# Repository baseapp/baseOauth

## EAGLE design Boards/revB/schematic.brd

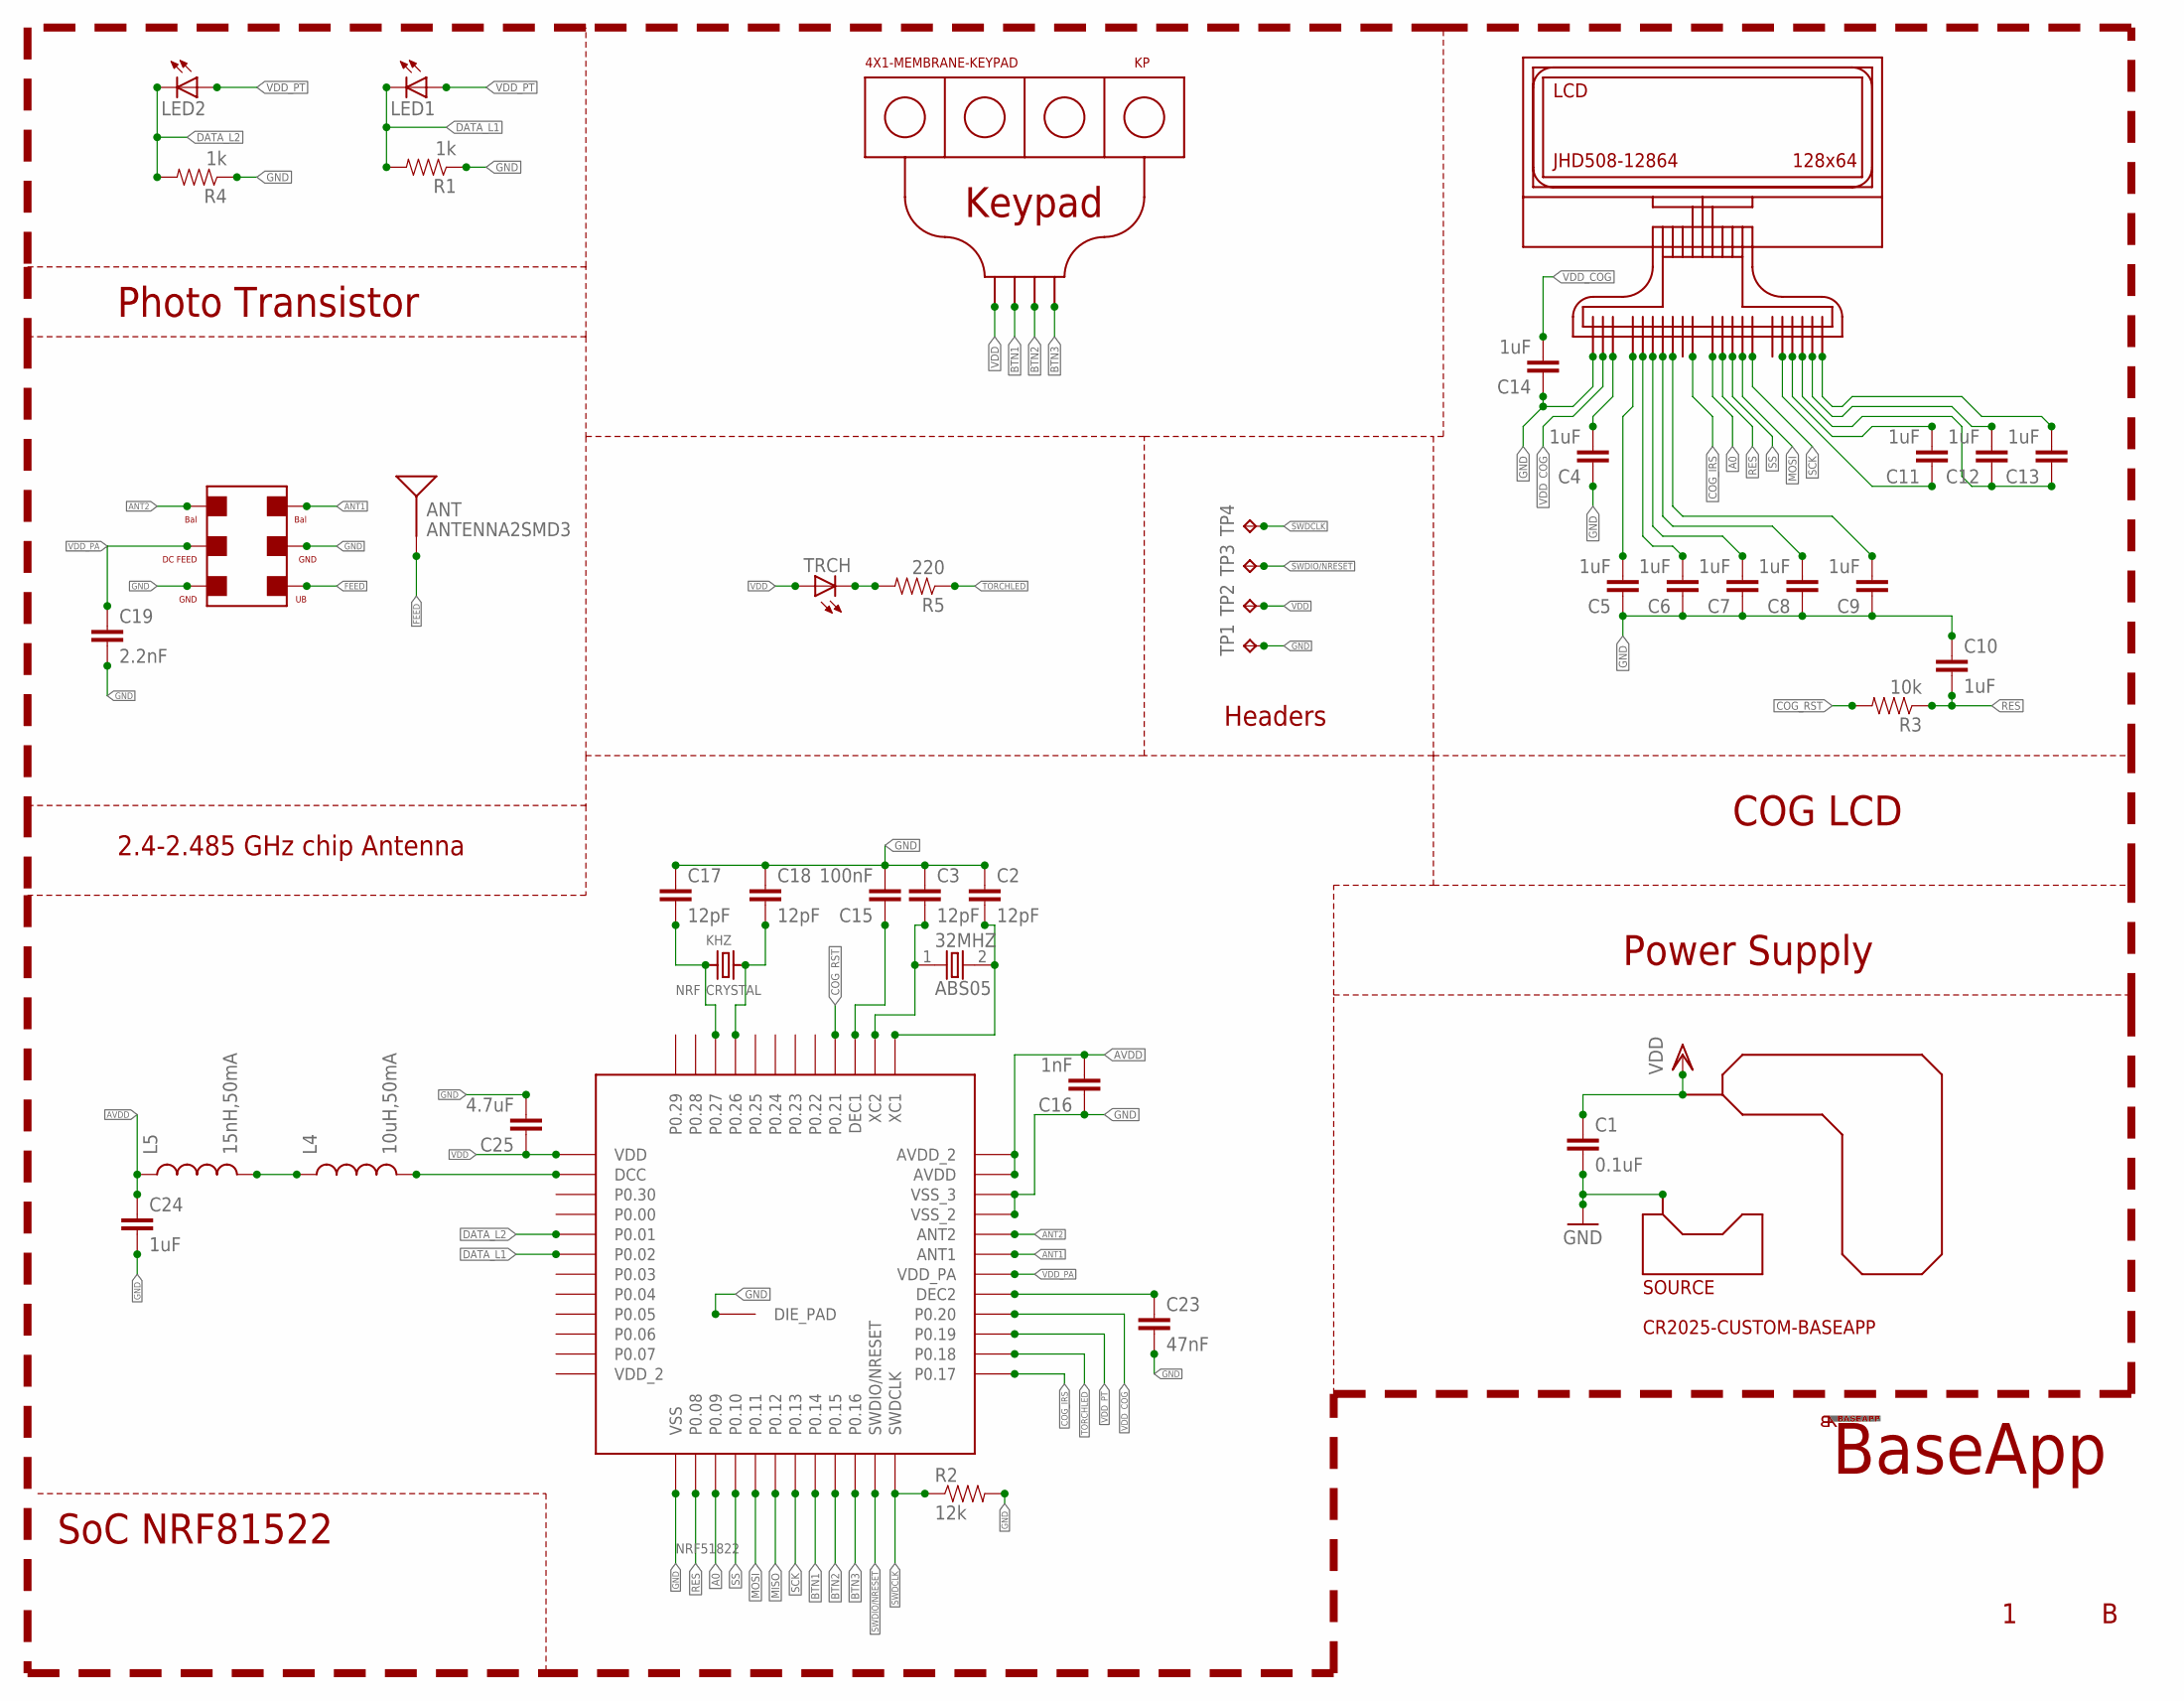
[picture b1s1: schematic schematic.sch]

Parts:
32MHZ: ABS05
ANT: ANTENNA2SMD3; ANTENNA-CHIP4
BU: 2450BM14E0003_BALUN; 6PCPADS
C1: 0.1uF; 0402-CAP
C2, C3, C17, C18: 12pF; 0402-CAP
C4, C5, C6, C7, C8, C9, C10, C11, C12, C13, C14, C24: 1uF; 0402-CAP
C15: 100nF; 0402-CAP
C16: 1nF; 0402-CAP
C19: 2.2nF; 0402-CAP
C23: 47nF; 0402-CAP
C25: 4.7uF; 0402-CAP
KHZ: CRYSTAL; ABS05
KP: 4X1-MEMBRANE-KEYPAD
L4: 10uH,50mA; C0402
L5: 15nH,50mA; C0402
LCD: JHD508-12864; FSTN
LED1, LED2: LEDCHIP-LED0805; CHIP-LED0805
NRF: NRF51822; QFN48
R1, R4: 1k; 0402-RES
R2: 12k; 0402-RES
R3: 10k; 0402-RES
R5: 220; 0402-RES
SOURCE: CR2025-CUSTOM-BASEAPP
TP1, TP2, TP3, TP4: TPTP06SQ; TP06SQ
TRCH: LEDSML0603; SML0603

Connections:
A0: LCD.P$19 (A0), NRF.15 (P0.09)
ANT1: BU.P$3 (3), NRF.31 (ANT1)
ANT2: BU.P$4 (4), NRF.32 (ANT2)
AVDD: C16.2, C24.1, L5.1, NRF.35 (AVDD), NRF.36 (AVDD_2)
BTN1: KP.P$2, NRF.20 (P0.14)
BTN2: KP.P$3, NRF.21 (P0.15)
BTN3: KP.P$4, NRF.22 (P0.16)
COG_IRS: LCD.P$1 (IRS), NRF.25 (P0.17)
COG_RST: NRF.40 (P0.21), R3.2
DATA_L1: LED1.C, NRF.6 (P0.02), R1.2
DATA_L2: LED2.C, NRF.5 (P0.01), R4.2
FEED: ANT.SIG, BU.P$1 (1)
GND: BU.P$2 (2), BU.P$6 (6), C1.2, C2.1, C3.1, C4.1, C5.1, C6.1, C7.1, C8.1, C9.1, C10.1, C14.1, C15.2, C16.1, C17.1, C18.1, C19.2, C23.2, C24.2, C25.2, LCD.P$15 (GND), NRF.13 (VSS), NRF.33 (VSS_2), NRF.34 (VSS_3), NRF.GND (DIE_PAD), R1.1, R2.2, R4.1, SOURCE.1 (GND), TP1.TP
MISO: NRF.18 (P0.12)
MOSI: LCD.P$17 (SI), NRF.17 (P0.11)
unnamed: C11.2, LCD.P$10 (CAP2N)
unnamed: C18.2, KHZ.P$2 (2), NRF.45 (P0.26)
unnamed: C4.2, LCD.P$14 (VOUT)
unnamed: C5.2, LCD.P$7 (V1)
unnamed: C15.1, NRF.39 (DEC1)
unnamed: C6.2, LCD.P$6 (V2)
unnamed: C7.2, LCD.P$5 (V3)
unnamed: C8.2, LCD.P$4 (V4)
unnamed: C9.2, LCD.P$3 (V5)
unnamed: C12.2, LCD.P$12 (CAP1P)
unnamed: C12.1, C13.1, LCD.P$11 (CAP1N)
unnamed: 32MHZ.1, C3.2, NRF.38 (XC2)
unnamed: 32MHZ.2, C2.2, NRF.37 (XC1)
unnamed: C23.1, NRF.29 (DEC2)
unnamed: C17.2, KHZ.P$1 (1), NRF.46 (P0.27)
unnamed: L4.2, NRF.2 (DCC)
unnamed: C11.1, LCD.P$9 (CAP2P)
unnamed: L4.1, L5.2
unnamed: R5.2, TRCH.C
unnamed: C13.2, LCD.P$13 (CAP3N)
RES: C10.2, LCD.P$20 (/RES), NRF.14 (P0.08), R3.1
SCK: LCD.P$18 (SCL), NRF.19 (P0.13)
SS: LCD.P$21 (/CS1), NRF.16 (P0.10)
SWDCLK: NRF.24 (SWDCLK), R2.1, TP4.TP
SWDIO/NRESET: NRF.23 (SWDIO/NRESET), TP3.TP
TORCHLED: NRF.26 (P0.18), R5.1
VDD: C1.1, C25.1, KP.P$1, NRF.1 (VDD), SOURCE.2 (VDD), TP2.TP, TRCH.A
VDD_COG: C14.2, LCD.P$16 (VDD), NRF.28 (P0.20)
VDD_PA: BU.P$5 (5), C19.1, NRF.30 (VDD_PA)
VDD_PT: LED1.A, LED2.A, NRF.27 (P0.19)

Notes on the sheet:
Power Supply
SoC NRF81522
Keypad
COG LCD
Photo Transistor
BaseApp
2.4-2.485 GHz chip Antenna
Headers

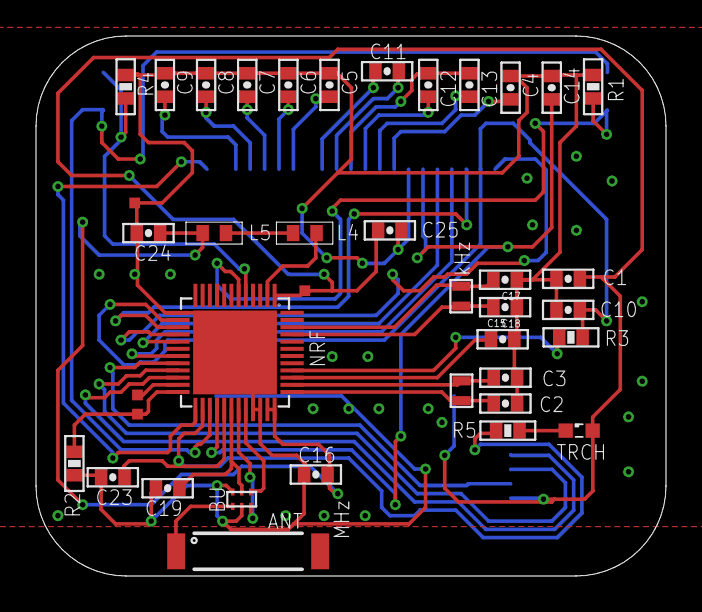
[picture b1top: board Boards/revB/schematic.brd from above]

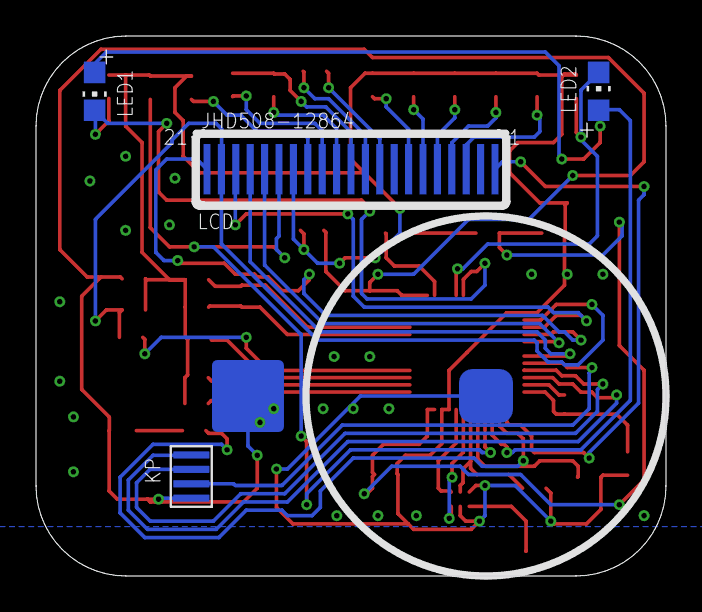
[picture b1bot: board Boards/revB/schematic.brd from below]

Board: 2 copper layers, 35.0 x 30.0 mm, 44 parts (5 on the bottom side), 44 nets.

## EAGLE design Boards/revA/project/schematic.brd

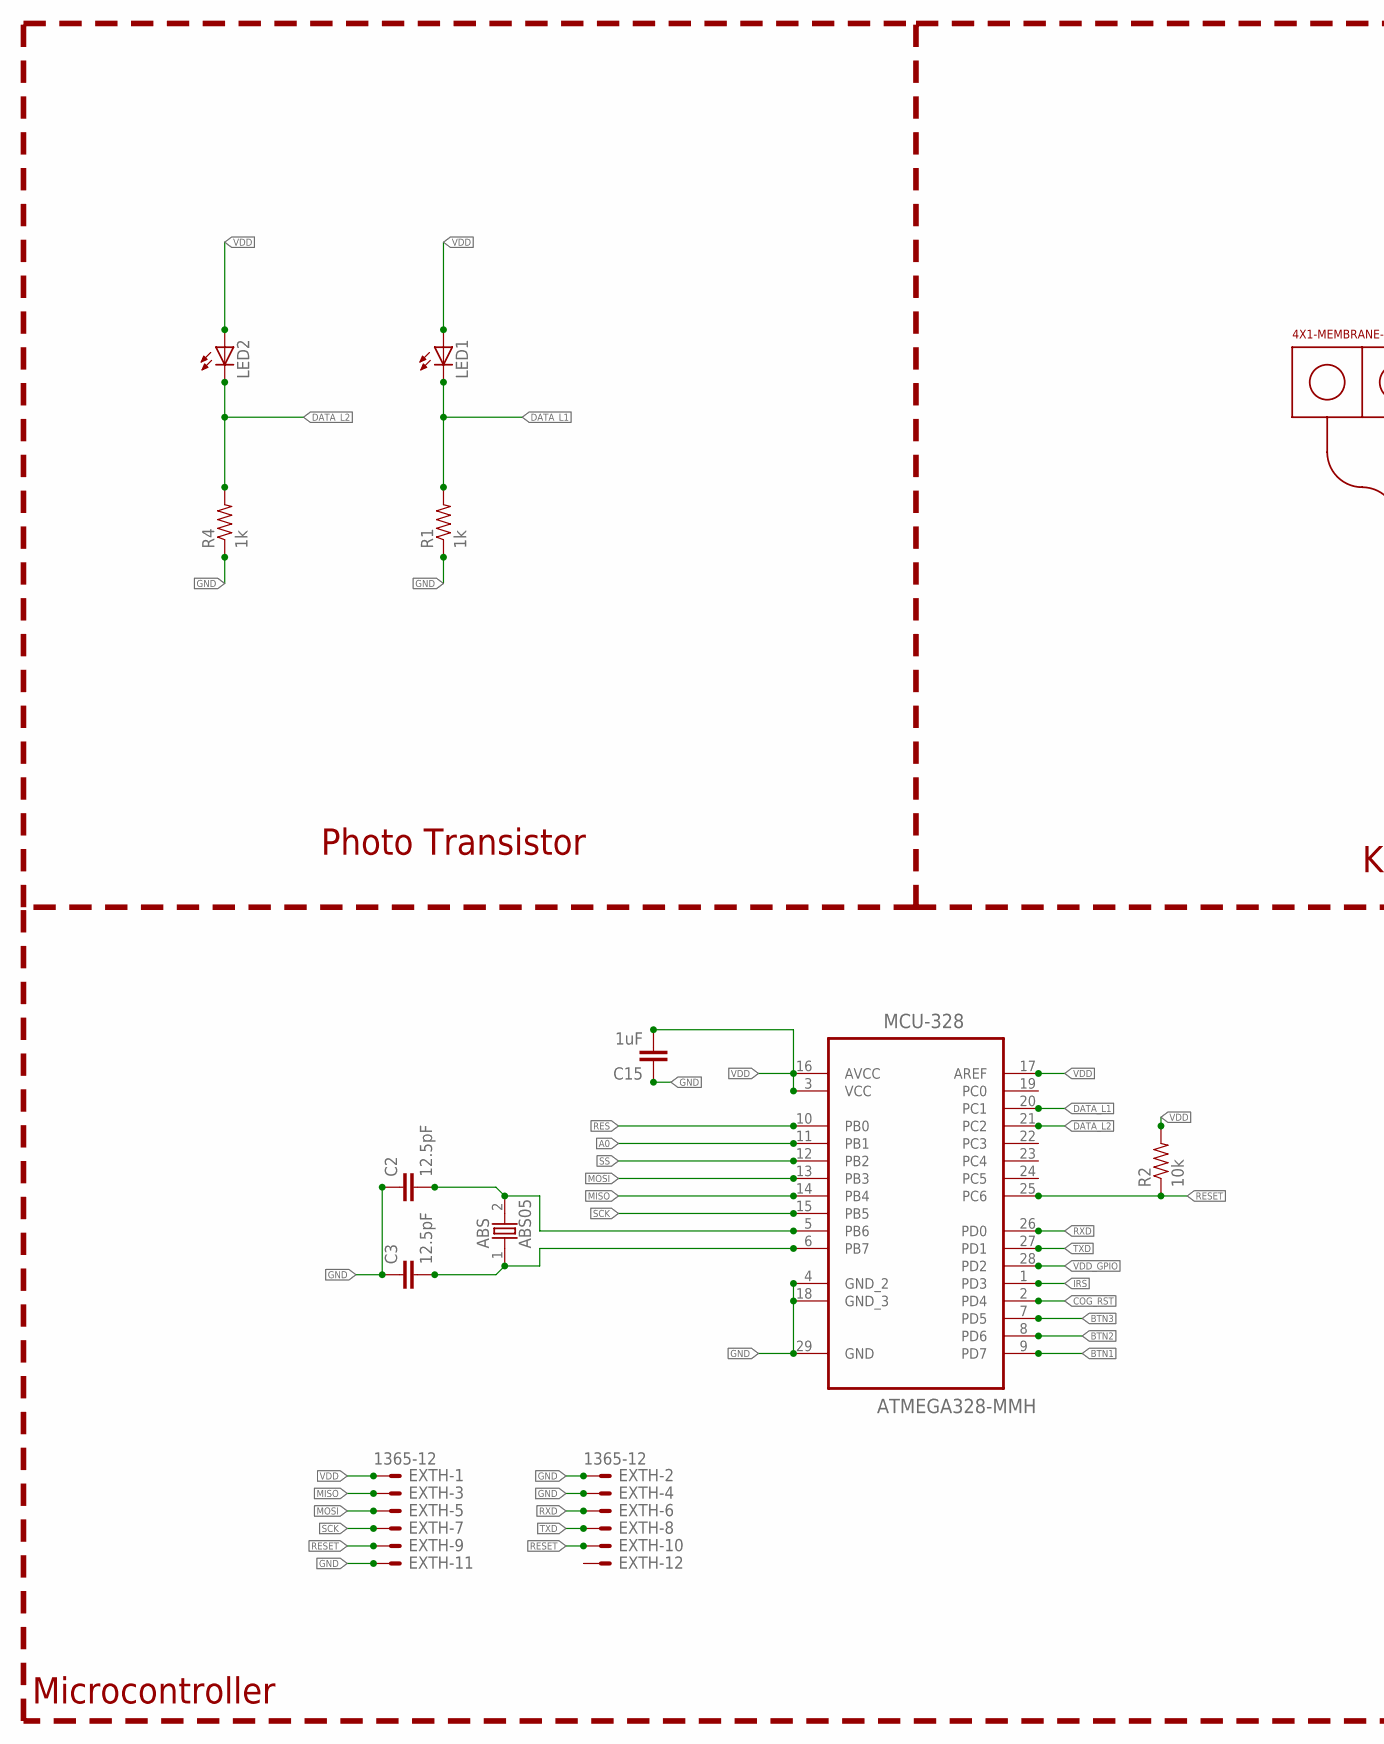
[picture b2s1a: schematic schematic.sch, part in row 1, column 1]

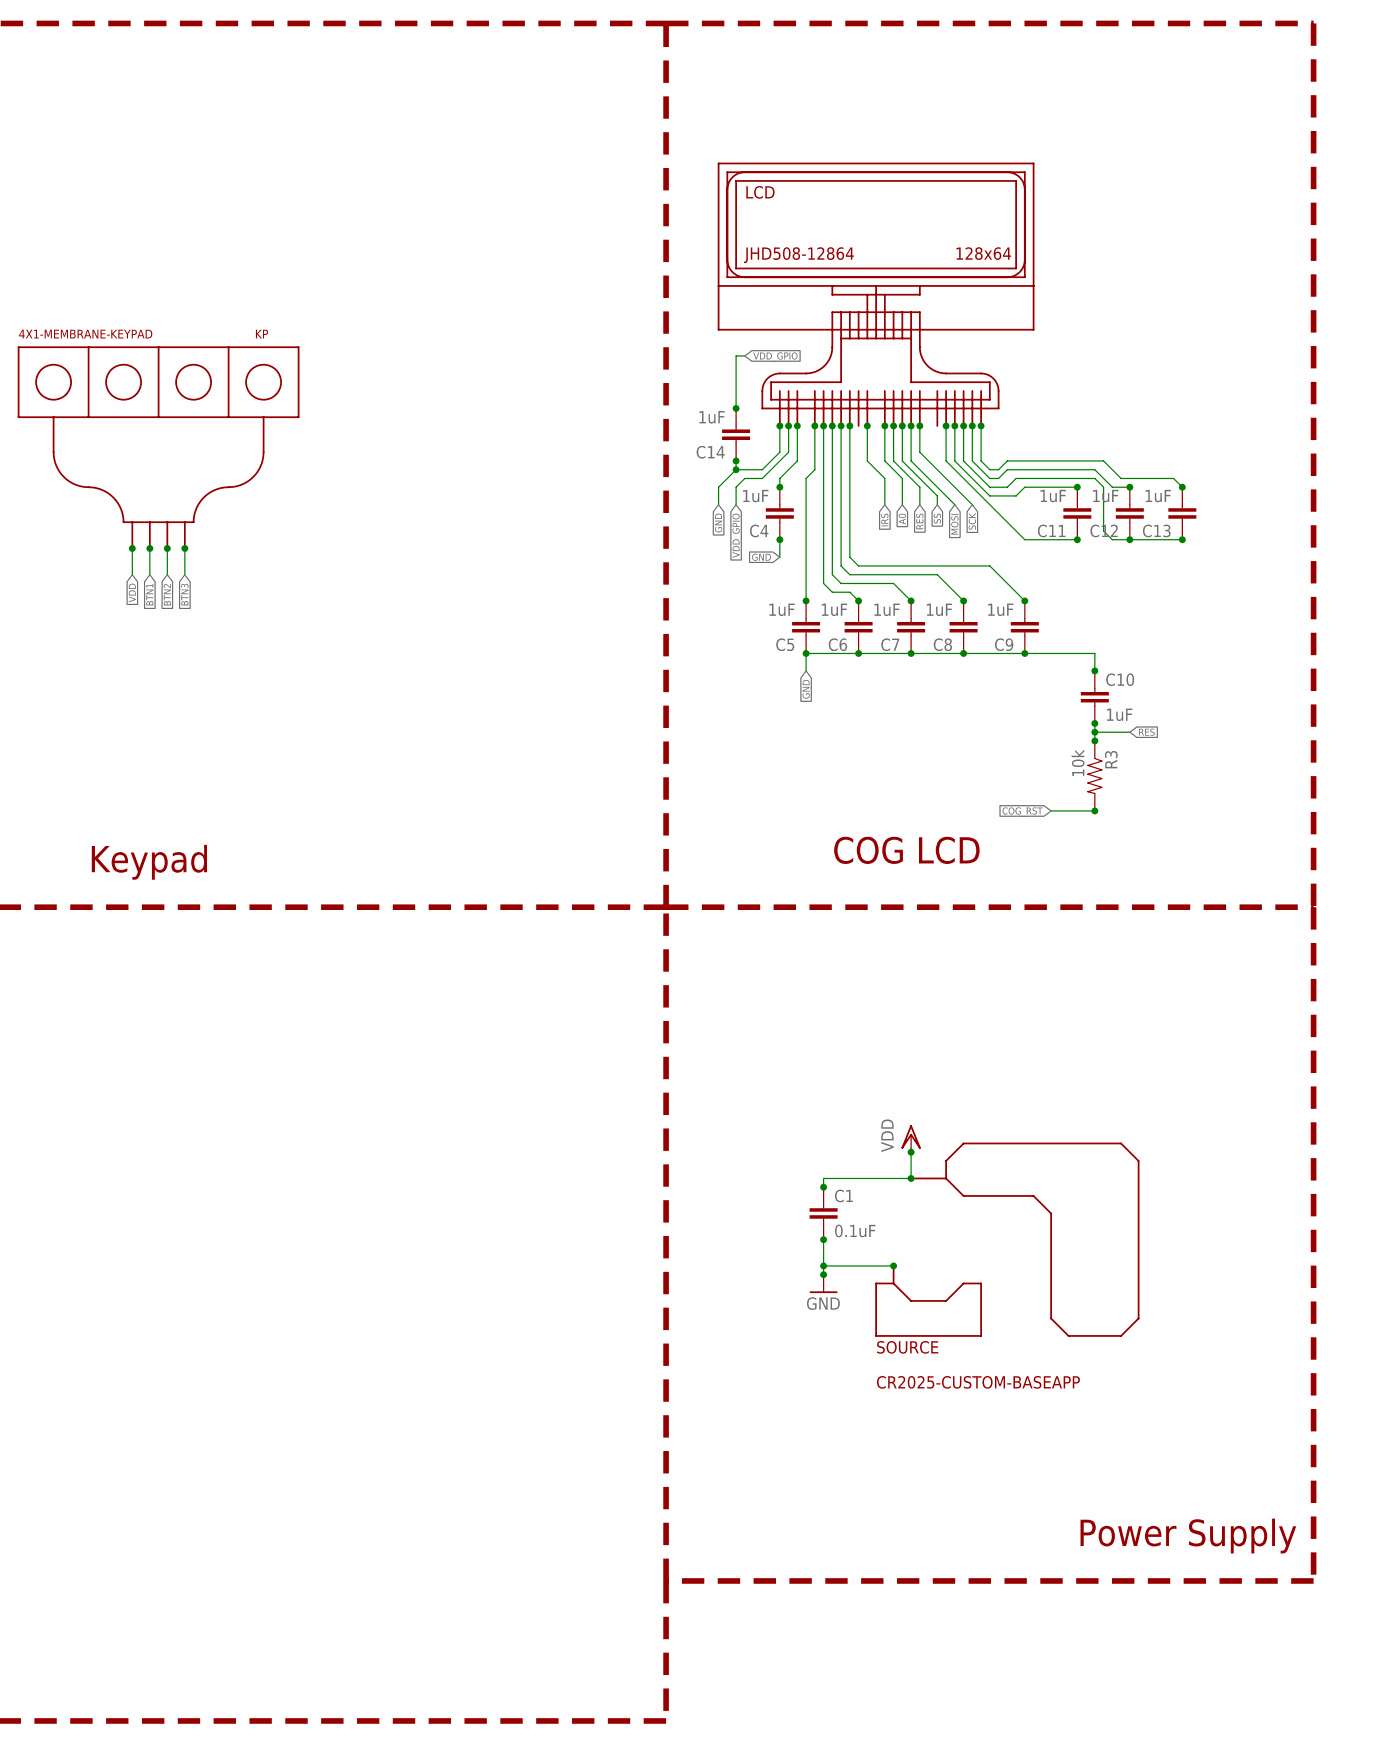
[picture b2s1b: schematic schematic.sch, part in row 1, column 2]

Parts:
ABS: ABS05
C1: 0.1uF; 0402-CAP
C2, C3: 12.5pF; 0402-CAP
C4, C5, C6, C7, C8, C9, C10, C11, C12, C13, C14, C15: 1uF; 0402-CAP
EXTH: 1365-12
KP: 4X1-MEMBRANE-KEYPAD
LCD: JHD508-12864; FSTN
LED1, LED2: LEDCHIP-LED0805; CHIP-LED0805
MCU-328: ATMEGA328-MMH; QFN45P400X400X100-29N
R1, R4: 1k; 0402-RES
R2, R3: 10k; 0402-RES
SOURCE: CR2025-CUSTOM-BASEAPP

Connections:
A0: LCD.P$19 (A0), MCU-328.11 (PB1)
BTN1: KP.P$2, MCU-328.9 (PD7)
BTN2: KP.P$3, MCU-328.8 (PD6)
BTN3: KP.P$4, MCU-328.7 (PD5)
COG_RST: MCU-328.2 (PD4), R3.2
DATA_L1: LED1.C, MCU-328.20 (PC1), R1.2
DATA_L2: LED2.C, MCU-328.21 (PC2), R4.2
GND: C1.2, C2.1, C3.1, C4.1, C5.1, C6.1, C7.1, C8.1, C9.1, C10.1, C14.1, C15.1, EXTH.2, EXTH.4, EXTH.11, LCD.P$15 (GND), MCU-328.4 (GND_2), MCU-328.18 (GND_3), MCU-328.29 (GND), R1.1, R4.1, SOURCE.1 (GND)
IRS: LCD.P$1 (IRS), MCU-328.1 (PD3)
MISO: EXTH.3, MCU-328.14 (PB4)
MOSI: EXTH.5, LCD.P$17 (SI), MCU-328.13 (PB3)
unnamed: C11.2, LCD.P$10 (CAP2N)
unnamed: ABS.2, C2.2, MCU-328.5 (PB6)
unnamed: C4.2, LCD.P$14 (VOUT)
unnamed: C5.2, LCD.P$7 (V1)
unnamed: ABS.1, C3.2, MCU-328.6 (PB7)
unnamed: C6.2, LCD.P$6 (V2)
unnamed: C7.2, LCD.P$5 (V3)
unnamed: C8.2, LCD.P$4 (V4)
unnamed: C9.2, LCD.P$3 (V5)
unnamed: C12.2, LCD.P$12 (CAP1P)
unnamed: C12.1, C13.1, LCD.P$11 (CAP1N)
unnamed: C11.1, LCD.P$9 (CAP2P)
unnamed: C13.2, LCD.P$13 (CAP3N)
RES: C10.2, LCD.P$20 (/RES), MCU-328.10 (PB0), R3.1
RESET: EXTH.9, EXTH.10, MCU-328.25 (PC6), R2.1
RXD: EXTH.6, MCU-328.26 (PD0)
SCK: EXTH.7, LCD.P$18 (SCL), MCU-328.15 (PB5)
SS: LCD.P$21 (/CS1), MCU-328.12 (PB2)
TXD: EXTH.8, MCU-328.27 (PD1)
VDD: C1.1, C15.2, EXTH.1, KP.P$1, LED1.A, LED2.A, MCU-328.3 (VCC), MCU-328.16 (AVCC), MCU-328.17 (AREF), R2.2, SOURCE.2 (VDD)
VDD_GPIO: C14.2, LCD.P$16 (VDD), MCU-328.28 (PD2)

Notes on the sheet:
Power Supply
Microcontroller
Keypad
COG LCD
Photo Transistor

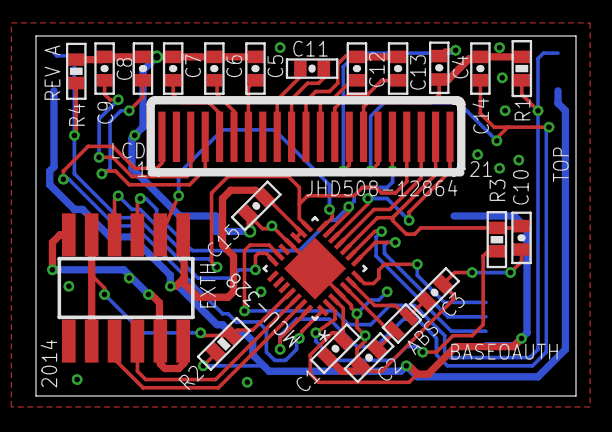
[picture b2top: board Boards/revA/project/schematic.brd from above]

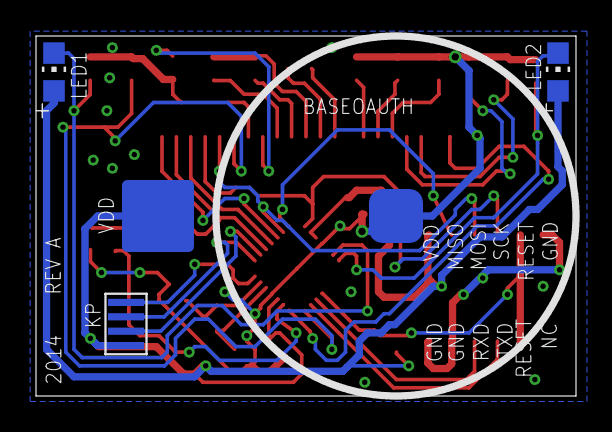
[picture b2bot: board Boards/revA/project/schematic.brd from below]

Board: 2 copper layers, 30.0 x 20.0 mm, 27 parts (4 on the bottom side), 32 nets.

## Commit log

2014-10-28 normal Push.
2014-12-02 LED ADDED and Component Placed.
2014-12-09 Normal Push.rev B Routed

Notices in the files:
parts and their libraries:
SparkFun-Passives: Licensing: Creative Commons ShareAlike 4.0 International - https://creativecommons.org/licenses/by-sa/4.0
SparkFun-RF: Licensing: CC v3.0 Share-Alike You are welcome to use this library for commercial purposes.
